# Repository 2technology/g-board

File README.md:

# G-board V 0.1!
PCB design in order to use a ESP32 DevkitC to drive a relay and 4 seperate WS2812b-channels. It has terminal blocks for easy installation and up to 4 pushbuttons can be connected. It uses a Logic level shifter to communicate with the WS2812b led drivers. **Use case:** Smart lights room controller for Home assistant (ESP32 firmware created with ESPHome).

  - [ESP32 DEVKIT C 32D](https://www.aliexpress.com/item/4000434690235.html)
  - 4 * I2C connection headers
  - 1 * 12V Relay rated 16A ([Schrack RTD34012](https://www.tme.eu/en/details/rtd34012/miniature-electromagnetic-relays/te-connectivity/3-1419108-5/) )
  - 4 * WS2812b LED Output channels (with Logic Level Shifter [74HCT245N](https://www.aliexpress.com/item/4000115614415.html))
  - 4 * debounced pushbutton inputs

### Features
#### 12V Relay rated 16A ([Schrack RTD34012](https://www.tme.eu/en/details/rtd34012/miniature-electromagnetic-relays/te-connectivity/3-1419108-5/) )

#### 4 debounced pushbutton inputs

#### 4 WS2812b LED Output channels (with Logic Level Shifter [74HCT245N](https://www.aliexpress.com/item/4000115614415.html))

### Schematic and PCB
View [Schematic (pdf)](https://github.com/2technology/g-board/blob/master/G-Board%20V0.1%20-%20Schematic.pdf)

Download KiCAD files: [Schematic](https://github.com/2technology/g-board/blob/master/G-board_V0_1.sch), [PCB](https://github.com/2technology/g-board/blob/master/G-board_V0_1.kicad_pcb)

### Gerbers
Download [Gerbers](https://github.com/2technology/g-board/blob/master/gerbers.zip)
### BOM

### Licence
[GPL-3.0](https://github.com/2technology/g-board/blob/master/LICENSE)

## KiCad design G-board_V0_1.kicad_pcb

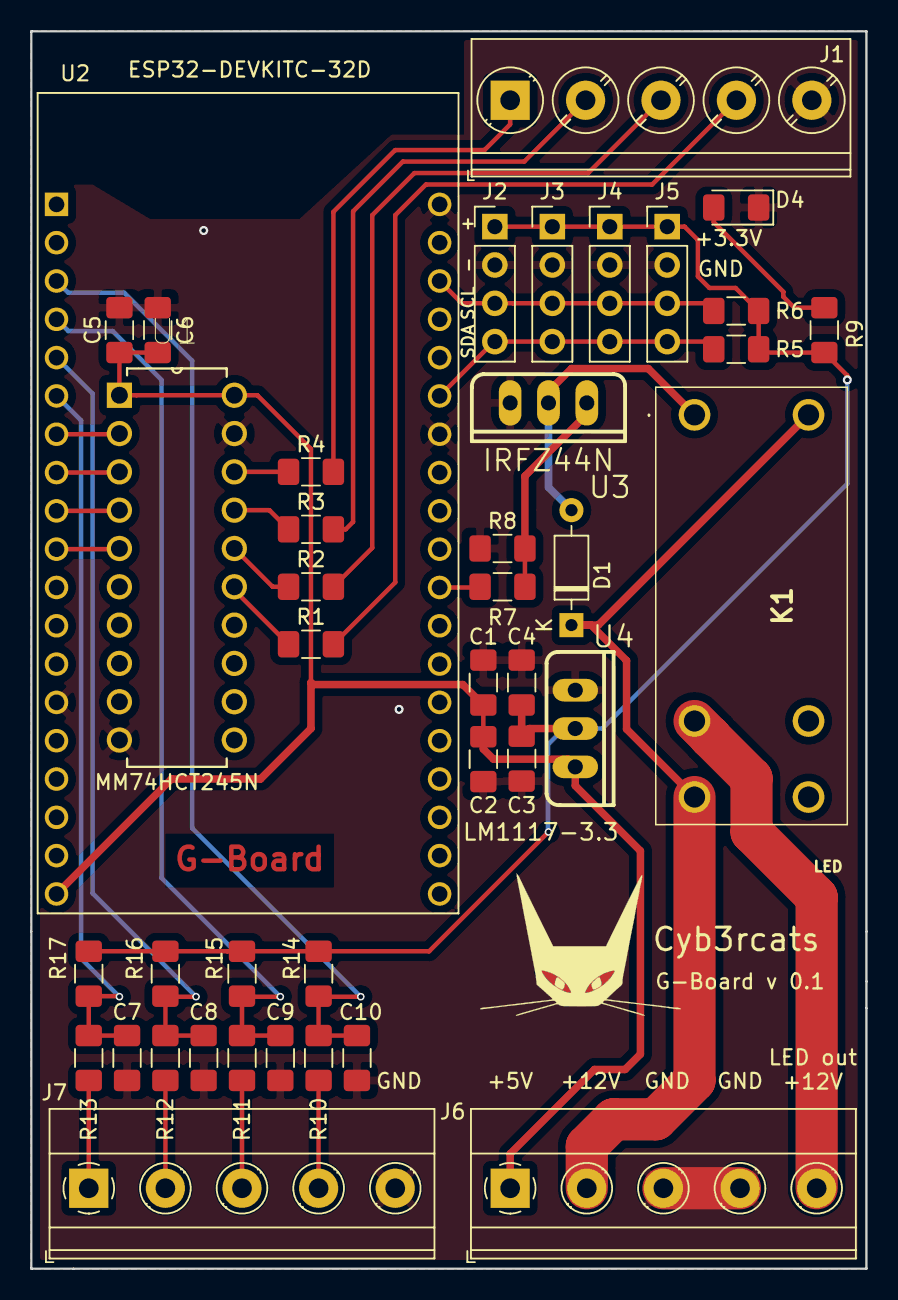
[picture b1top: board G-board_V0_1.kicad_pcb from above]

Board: 2 copper layers, 55.4 x 82.0 mm, 42 parts (0 on the bottom side), 31 nets.

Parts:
*: Cyb3rcats; cybercats_logo_silk_cu
C1, C4, C5: 0.1μF; R_1206_3216Metric_Pad1.42x1.75mm_HandSolder
C2, C3, C6: 10μF; R_1206_3216Metric_Pad1.42x1.75mm_HandSolder
C7, C8, C9, C10: 1nF; R_1206_3216Metric_Pad1.42x1.75mm_HandSolder
D1: 1N4148; D_DO-35_SOD27_P7.62mm_Horizontal
D4: LED; LED_1206_3216Metric_Pad1.42x1.75mm_HandSolder
J1: aRGB LEDs; TerminalBlock_Phoenix_PT-1,5-5-5.0-H_1x05_P5.00mm_Horizontal
J2, J3, J4, J5: I2C; PinHeader_1x04_P2.54mm_Vertical
J6: POWER + LED; TerminalBlock_Phoenix_MKDS-1,5-5-5.08_1x05_P5.08mm_Horizont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
J7: Schakelaars; TerminalBlock_Phoenix_MKDS-1,5-5-5.08_1x05_P5.08mm_Horizont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
K1: RTD34012
R1, R2, R3, R4: 330Ω; R_1206_3216Metric_Pad1.42x1.75mm_HandSolder
R5, R6: 4.7kΩ; R_1206_3216Metric_Pad1.42x1.75mm_HandSolder
R7: 1kΩ; R_1206_3216Metric_Pad1.42x1.75mm_HandSolder
R8, R14, R15, R16, R17: 10kΩ; R_1206_3216Metric_Pad1.42x1.75mm_HandSolder
R9: 1k; R_1206_3216Metric_Pad1.42x1.75mm_HandSolder
R10, R11, R12, R13: 220Ω; R_1206_3216Metric_Pad1.42x1.75mm_HandSolder
U1: MM74HCT245N; DIP254P762X508-20
U2: ESP32-DEVKITC-32D; MODULE_ESP32-DEVKITC-32D
U3: IRFZ44N; TO-220
U4: LM1117-3.3; TO-220

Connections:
+3V3: C3.1, C4.1, J2.1, J3.1, J4.1, J5.1, R5.2, R6.2, R9.2, R14.2, R15.2, R16.2, R17.2, U4.2
+5V: C1.1, C2.1, C5.2, C6.2, J6.1, U1.1, U1.20, U2.19, U4.3
+12V: D1.1, J6.2, K1.3, K1.6
/SCL: J2.3, J3.3, J4.3, J5.3, R6.1, U2.22
/SDA: J2.4, J3.4, J4.4, J5.4, R5.1, U2.25
/aRGB1: J1.1, R4.2
/relay: R7.2, U2.30
/switch1: C7.1, R13.2, R17.1, U2.6
/switch2: C8.1, R12.2, R16.1, U2.5
/switch3: C9.1, R11.2, R15.1, U2.4
/switch4: C10.1, R10.2, R14.1, U2.3
GND: C1.2, C2.2, C3.2, C4.2, C5.1, C6.1, C7.2, C8.2, C9.2, C10.2, D4.1, J1.5, J2.2, J3.2, J4.2, J5.2, J6.3, J6.4, J7.5, R8.1, U1.10, U1.19, U2.14, U2.20, U2.26, U3.3, U4.1
unnamed: D1.2, K1.1, U3.2
unnamed: D4.2, R9.1
unnamed: J1.2, R3.2
unnamed: J1.3, R2.2
unnamed: J1.4, R1.2
unnamed: J6.5, K1.2
unnamed: J7.1, R13.1
unnamed: J7.2, R12.1
unnamed: J7.3, R11.1
unnamed: J7.4, R10.1
unnamed: R1.1, U1.15
unnamed: R2.1, U1.16
unnamed: R3.1, U1.17
unnamed: R4.1, U1.18
unnamed: R7.1, R8.2, U3.1
unnamed: U1.2, U2.7
unnamed: U1.3, U2.8
unnamed: U1.4, U2.9
unnamed: U1.5, U2.10
